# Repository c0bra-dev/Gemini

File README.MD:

Gemini
The goal of this project is to make the integration of constant speed motor controlling easy and user-friendly and to remove the hassle of building custom solutions for every project that requires this feature.
This is achieved by allowing an easy connection to encoders and by having multiple ways to communicate such as WiFi, USB, I2C, UART and direct PWM. Our hardware is also capable of sensorless closed loop control, but it is not yet implemented in software and will be available as an update.
An easy GUI will let users quickly set up the board for any specific application they need. It is still in early development process, but we aim to showcase it at ROME MRF19.
Project is released as both open hardware and open source.
Software is released under MIT licence and hardware under CERN Open Hardware Licence.

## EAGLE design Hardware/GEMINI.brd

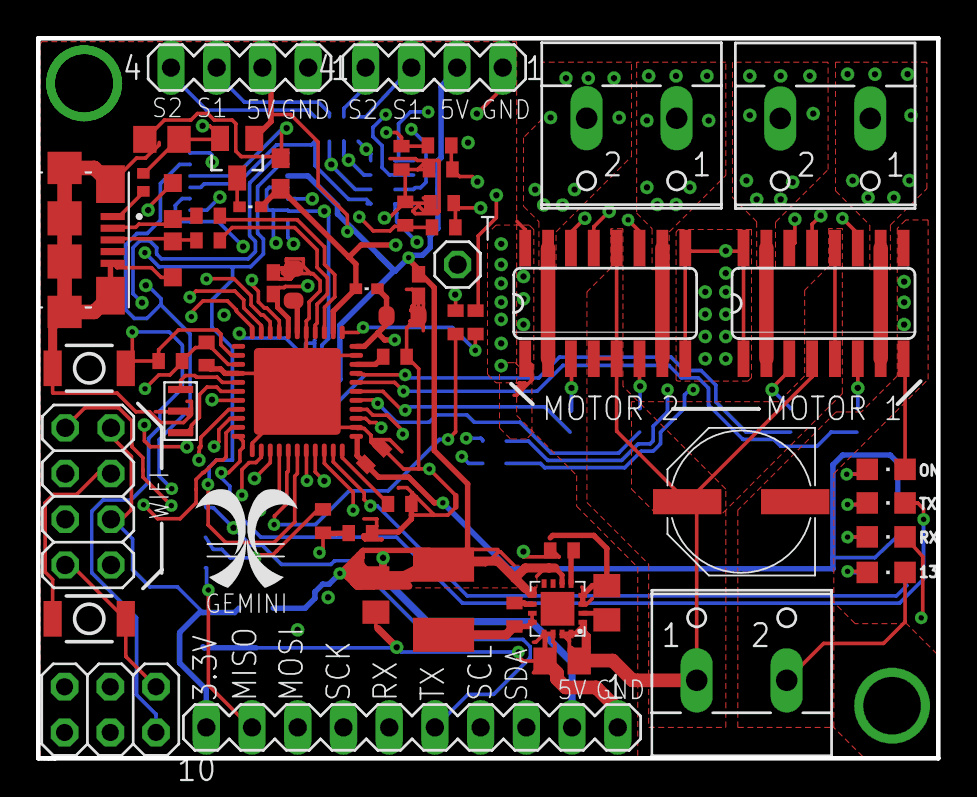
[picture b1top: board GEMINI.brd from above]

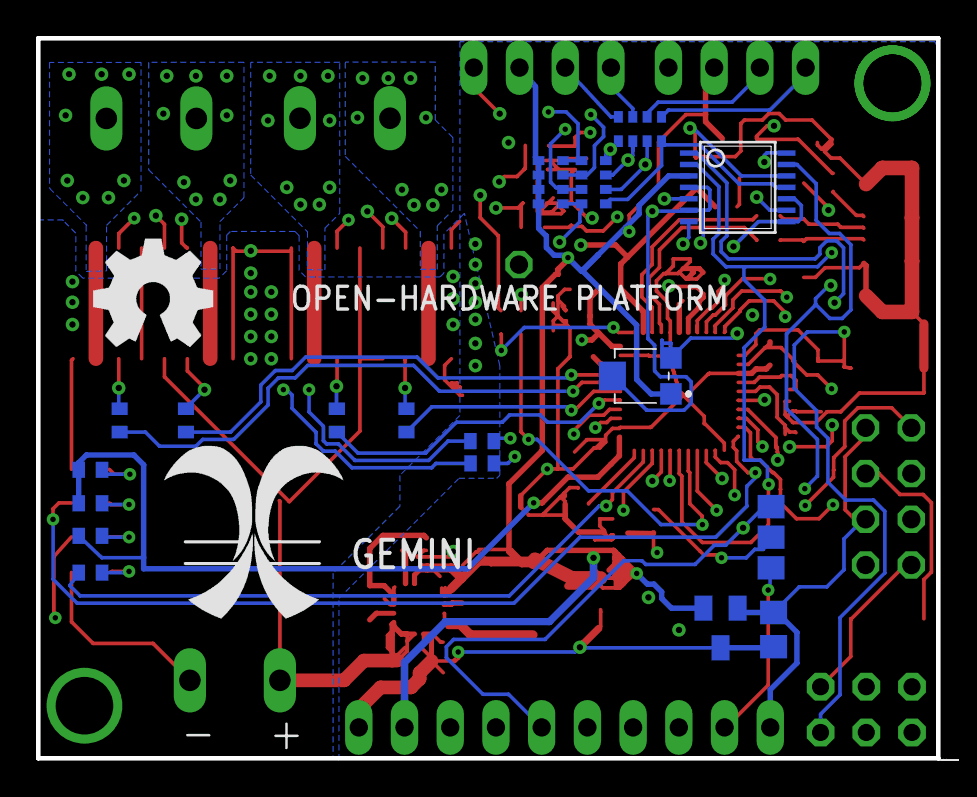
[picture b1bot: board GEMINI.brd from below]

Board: 4 copper layers, 50.0 x 40.0 mm, 75 parts (18 on the bottom side), 77 nets.

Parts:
C1: 2.2uF; C0603
C2, C4: 10uF; C0805
C3, C13: 100n; C0402K
C5, C7: 1uF; C0603-ROUND
C6, C8, C11: 100n; C0402
C9, C10: 10n; C0402
C12: PANASONIC_E
C36, C40: 2.2uF; C0805
C37: 0.1uF; C0402
C38: 22uF; C0805
C39: 5600pF; C0402
D3: SDM40E20LC-7; SOT23
ICSP: ICSP; 2X03
J1: ZX62-B-5PA(33); HRS_ZX62-B-5PA(33)
JMP1: 0R-JUMPB; B0R-JMP
JP5: 2X04
L1, L2: MPZ1005A331ETD25; 0402
L8: 10uH; RCL_L1812
LED: BLUE; CHIPLED_0805
LM2901AQT14-13: LM390; TSSOP14
MOT1, MOT2: W237-102
ON: Green; CHIPLED_0805
POWER: W237-102
R1, R2, R3, R6, R7, R20, R22, R24, R25, R26, R28, R30, R31: 1k; R0402
R4, R21, R27: 10k; R0402
R5: 690; R0402
R8: 2k; R0402
R9, R10: 22; R0402
R23, R29: 4k; R0402
RESET, RESET1: SMD_157SW
RN1: 10k; CAT16
RN2: 3k; CAT16
RN3: 10M; CAT16
RX: Yellow; CHIPLED_0805
SV1, SV2: MA04-1
SV3: MA10-1
T: 1X01
TX: Yellow; CHIPLED_0805
U1: ATMEGA32U4-XUMU; QFN44ML7X7
U$1: RISONATORE
U$3: MAX17632B; QFN16
U$5: MCP1812BT-3.3; SOT23
U$6: F0402E0R50FSTR; R0402
U$29, U$32: VNH7070; SO16
VR1: 35WR10KLFTR; 35WR100KLFTR
Z1, Z2: CG0603MLC-05E; CT/CN0603

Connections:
+3V3: C4.1, JP5.2, JP5.6, SV3.10, U$5.1
+5V: C3.2, C38.1, D3.1, L8.1, LM2901AQT14-13.VCC, RN2.1, RN2.2, RN2.3, RN2.4, SV1.2, SV2.2, SV3.2, U$3.6, U$3.9, U$5.2, VR1.1
+5VP: C1.1, C8.1, C11.1, ICSP.2, L1.1, L2.2, R3.1, R4.2, R6.1, R7.1, U1.2, U1.14, U1.34
AREF: C6.2, U1.42
AVCC: C5.1, L1.2, U1.24, U1.44
D+: J1.3, R10.1, Z1.1
D-: J1.2, R9.1, Z2.1
E1I: RN1.8, SV2.3
E1M: LM2901AQT14-13.1OUT, RN2.8, RN3.5, U1.20
E2I: RN1.7, SV2.4
E2M: LM2901AQT14-13.2OUT, RN2.7, RN3.6, U1.28
E3I: RN1.6, SV1.3
E3M: LM2901AQT14-13.3OUT, RN2.6, RN3.7, U1.21
E4I: RN1.5, SV1.4
E4M: LM2901AQT14-13.4OUT, RN2.5, RN3.8, U1.29
GND: C1.2, C2.2, C3.1, C4.2, C5.2, C6.1, C7.2, C8.2, C9.1, C10.1, C11.2, C12.-, C13.1, C36.2, C38.2, C39.2, C40.2, ICSP.6, J1.5, J1.SH1, J1.SH2, J1.SH3, J1.SH4, J1.SH5, J1.SH6, JP5.7, LED.C, LM2901AQT14-13.GND, ON.C, POWER.2, R5.1, R8.2, R23.1, R29.1, RESET.2, RESET1.2, SV1.1, SV2.1, SV3.1, U1.5, U1.15, U1.23, U1.35, U1.43, U1.EXP, U$1.GND, U$3.3, U$3.4, U$3.13, U$3.14, U$5.3, U$29.1, U$29.8, U$29.9, U$29.16, U$32.1, U$32.8, U$32.9, U$32.16, VR1.3, Z1.2, Z2.2
HWB: R5.2, U1.33
M1_CS: C9.2, R21.1, U1.36
M1_INA: R24.2, U1.40
M1_INB: R25.2, U1.41
M1_PWM: R20.1, U1.26
M1_SEL: R22.1, U1.1
M2_CS: C10.2, R27.1, U1.37
M2_INA: R30.2, U1.38
M2_INB: R31.2, U1.39
M2_PWM: R26.1, U1.31
M2_SEL: R28.1, U1.27
MISO: ICSP.1, JMP1.1, SV3.9, U1.11
MOSI: ICSP.4, SV3.8, U1.10
MOT1_A: MOT1.1, U$29.7, U$29.10
MOT1_B: MOT1.2, U$29.2, U$29.15
MOT2_A: MOT2.1, U$32.7, U$32.10
MOT2_B: MOT2.2, U$32.2, U$32.15
unnamed: LED.A, R1.2
unnamed: LM2901AQT14-13.3IN+, RN1.3, RN3.2
unnamed: LM2901AQT14-13.4IN+, RN1.4, RN3.1
unnamed: ON.A, R3.2
unnamed: R6.2, RX.A
unnamed: R7.2, TX.A
unnamed: R21.2, R23.2, U$29.13
unnamed: R22.2, U$29.14
unnamed: R20.2, U$29.11
unnamed: R24.1, U$29.6
unnamed: R25.1, U$29.3
unnamed: R27.2, R29.2, U$32.13
unnamed: R28.2, U$32.14
unnamed: R26.2, U$32.11
unnamed: R30.1, U$32.6
unnamed: R31.1, U$32.3
unnamed: C37.2, U$3.10
unnamed: C37.1, L8.2, U$3.11, U$3.12
unnamed: C39.1, U$3.5
unnamed: C40.1, U$3.2
unnamed: R1.1, U1.32
unnamed: LM2901AQT14-13.1IN-, LM2901AQT14-13.2IN-, LM2901AQT14-13.3IN-, LM2901AQT14-13.4IN-, T.1, VR1.2
unnamed: D3.3, L2.1
unnamed: JP5.1, R2.2, R8.1
unnamed: JMP1.2, R2.1
unnamed: LM2901AQT14-13.2IN+, RN1.2, RN3.3
unnamed: LM2901AQT14-13.1IN+, RN1.1, RN3.4
unnamed: U1.17, U$1.IN
unnamed: U1.16, U$1.OUT
RD+: R10.2, U1.4
RD-: R9.2, U1.3
RESET: ICSP.5, R4.1, RESET.1, U1.13
RESET-WIFI: JP5.4, RESET1.1
RX: SV3.6, U1.30
RXLED: RX.C, U1.8
SCK: ICSP.3, SV3.7, U1.9
SCL: SV3.4, U1.18
SDA: SV3.3, U1.19
TX: JMP1.3, SV3.5, U1.25
TXLED: TX.C, U1.22
UCAP: C7.1, U1.6
VIN: C12.+, C36.1, POWER.1, U$3.1, U$3.15, U$3.16, U$29.4, U$29.5, U$29.12, U$32.4, U$32.5, U$32.12
VUSB: C2.1, C13.2, D3.2, U1.7, U$6.2
XUSB: J1.1, U$6.1

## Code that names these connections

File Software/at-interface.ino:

#include <SoftwareSerial.h>

/*
ERRATA: WIFI_RX is left unconnected
Connect the jumper up (to UART TX) and run a wire from WIFI RX to MISO

*/

#define E1 0
#define E2 8
#define E3 1
#define E4 9
#define UART_TX 4
#define UART_RX 10
#define SCLpin 3
#define SDApin 2
#define M1_PWM 12
#define M1_A A4
#define M1_B A5
#define M1_CS A0
#define M1_SEL 6
#define M2_PWM 5
#define M2_A A2
#define M2_B A3
#define M2_CS A1
#define M2_SEL 7

SoftwareSerial wifi_serial(MISO, UART_TX); // RX, TX

void setup() {
  Serial.begin(115200);
  wifi_serial.begin(115200);
  while (!Serial);
  Serial.println("Serial ESP_01 interface");
}
void loop() {
  if (Serial.available())wifi_serial.write(Serial.read());
  if (wifi_serial.available())Serial.write(wifi_serial.read());

}

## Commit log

2019-09-21 remove file1.txt
2019-09-21 add base project
2019-09-21 Create LICENSE
2019-10-28 gemini prod
2019-10-28 gemini prod fix
2019-10-28 motor test added
2019-10-29 Create install_linux
2019-10-29 Create install_windows
2019-10-29 Update install_windows
2020-03-14 Add files via upload
    at-interface errata
